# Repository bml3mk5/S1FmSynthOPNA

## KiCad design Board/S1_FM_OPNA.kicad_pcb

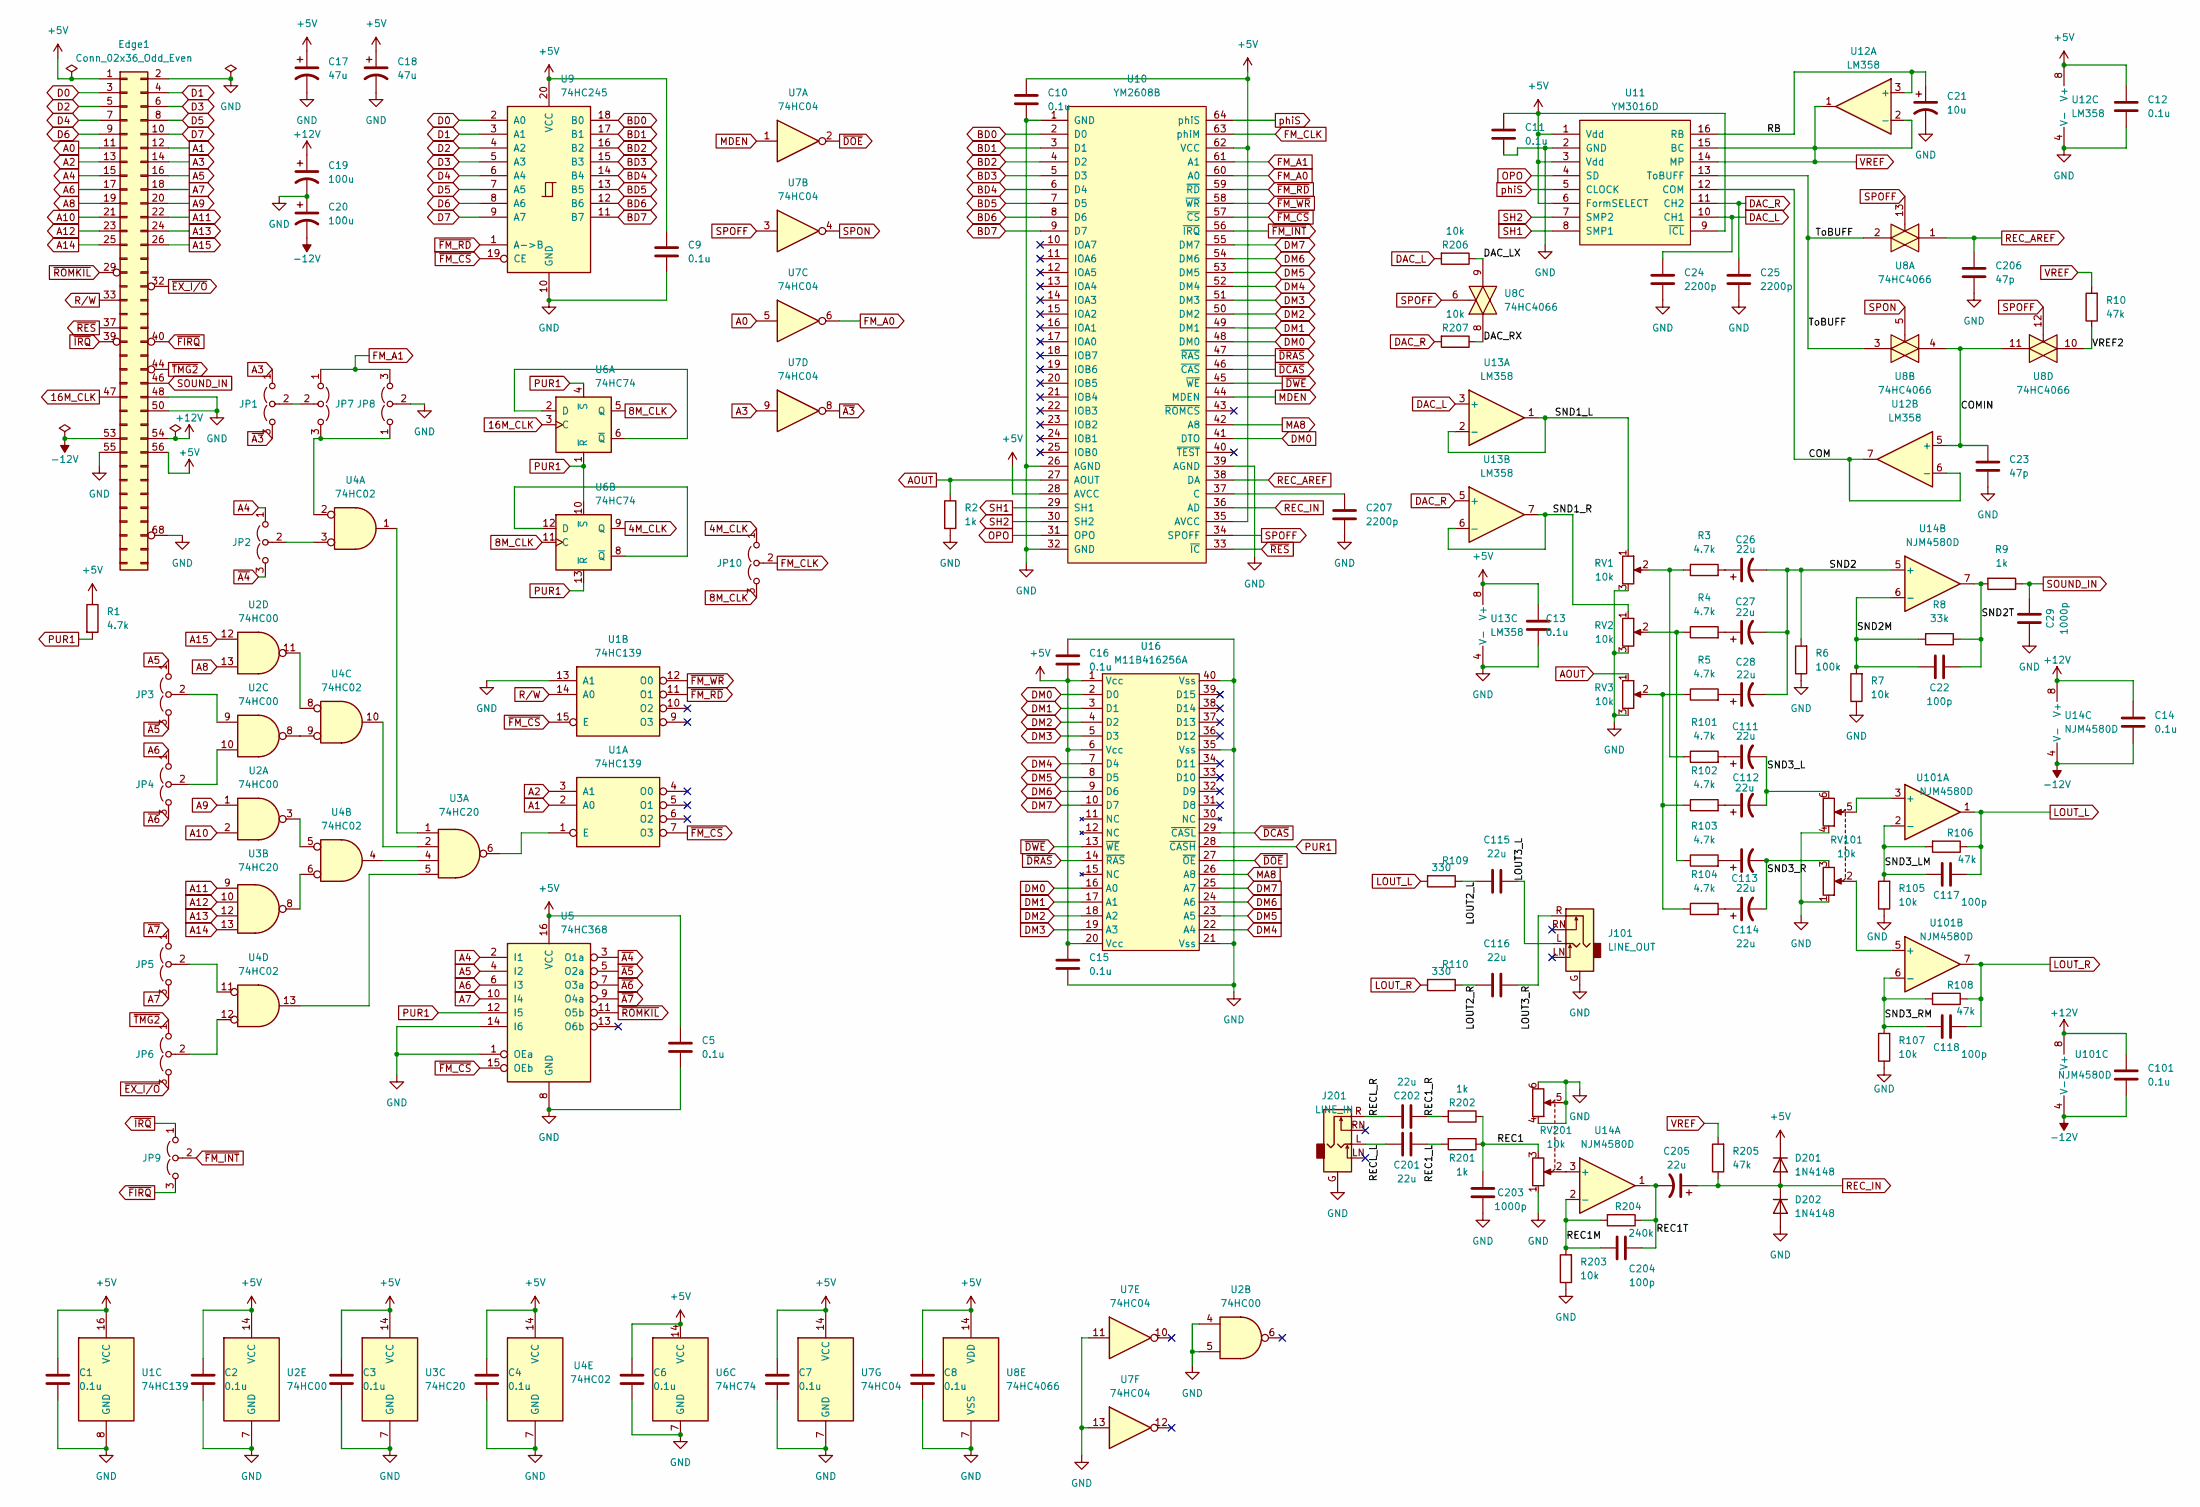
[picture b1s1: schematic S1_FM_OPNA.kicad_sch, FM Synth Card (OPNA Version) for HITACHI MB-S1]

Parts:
C1, C2, C3, C4, C5, C6, C7, C8, C9, C10, C11, C12, C13, C14, C15, C16, C101: 0.1u; C_Disc_D3.0mm_W1.6mm_P2.50mm
C17, C18: 47u; CP_Radial_D6.3mm_P2.50mm
C19, C20: 100u; CP_Radial_D6.3mm_P2.50mm
C21: 10u; CP_Radial_D5.0mm_P2.50mm
C22, C117, C118, C204: 100p; C_Disc_D3.0mm_W1.6mm_P2.50mm
C23, C206: 47p; C_Disc_D3.0mm_W1.6mm_P2.50mm
C24, C25, C207: 2200p; C_Disc_D3.0mm_W1.6mm_P2.50mm
C26, C27, C28, C111, C112, C113, C114, C205: 22u; CP_Radial_D5.0mm_P2.50mm
C29, C203: 1000p; C_Disc_D3.0mm_W1.6mm_P2.50mm
C115, C116, C201, C202: 22u; C_Radial_D6.3mm_H5.0mm_P2.50mm
D201, D202: 1N4148; D_DO-34_SOD68_P7.62mm_Horizontal
Edge1: Conn_02x36_Odd_Even; CardEdge72
J101: LINE_OUT; Jack_3.5mm_CUI_PJ317_Horizontal_X
J201: LINE_IN; Jack_3.5mm_CUI_PJ317_Horizontal_X
JP1, JP2, JP3, JP4, JP5, JP6, JP7, JP8, JP9, JP10: Jumper_3_Open; PinHeader_1x03_P2.54mm_Vertical
R1: 4.7k; R_Axial_DIN0207_L6.3mm_D2.5mm_P2.54mm_Vertical
R2, R9, R201, R202: 1k; R_Axial_DIN0207_L6.3mm_D2.5mm_P7.62mm_Horizontal
R3, R4, R5, R101, R102, R103, R104: 4.7k; R_Axial_DIN0207_L6.3mm_D2.5mm_P7.62mm_Horizontal
R6: 100k; R_Axial_DIN0207_L6.3mm_D2.5mm_P7.62mm_Horizontal
R7, R105, R107, R203, R206, R207: 10k; R_Axial_DIN0207_L6.3mm_D2.5mm_P7.62mm_Horizontal
R8: 33k; R_Axial_DIN0207_L6.3mm_D2.5mm_P7.62mm_Horizontal
R10, R106, R108, R205: 47k; R_Axial_DIN0207_L6.3mm_D2.5mm_P7.62mm_Horizontal
R109, R110: 330; R_Axial_DIN0207_L6.3mm_D2.5mm_P7.62mm_Horizontal
R204: 240k; R_Axial_DIN0207_L6.3mm_D2.5mm_P7.62mm_Horizontal
RV1, RV2, RV3: 10k; Potentiometer_Vishay_T73YP_Vertical
RV101, RV201: 10k; Potentiometer_Alps_RK097_Dual_Horizontal_X
U1: 74HC139; DIP-16_W7.62mm_Socket
U2: 74HC00; DIP-14_W7.62mm_Socket
U3: 74HC20; DIP-14_W7.62mm_Socket
U4: 74HC02; DIP-14_W7.62mm_Socket
U5: 74HC368; DIP-16_W7.62mm_Socket
U6: 74HC74; DIP-14_W7.62mm_Socket
U7: 74HC04; DIP-14_W7.62mm_Socket
U8: 74HC4066; DIP-14_W7.62mm_Socket
U9: 74HC245; DIP-20_W7.62mm_Socket
U10: YM2608B; SDIP-64
U11: YM3016D; DIP-16_W7.62mm_Socket
U12, U13: LM358; DIP-8_W7.62mm_Socket
U14, U101: NJM4580D; DIP-8_W7.62mm_Socket
U16: M11B416256A; SOIC-40

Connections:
4M_CLK: JP10.1 (A), U6.9 (Q)
8M_CLK: JP10.3 (B), U6.5 (Q), U6.11 (C)
16M_CLK: Edge1.47 (16M_CLK), U6.3 (C)
+5V: C1.1, C2.1, C3.1, C4.1, C5.1, C6.1, C7.1, C8.1, C9.1, C10.1, C11.1, C12.1, C13.1, C15.1, C16.2, C17.1, C18.1, D201.1 (K), Edge1.1 (Vcc), Edge1.56 (Vcc), R1.1, U1.16 (VCC), U2.14 (VCC), U3.14 (VCC), U4.14 (VCC), U5.16 (VCC), U6.14 (VCC), U7.14 (VCC), U8.14 (VDD), U9.20 (VCC), U10.28 (AVCC), U10.35 (AVCC), U10.62 (VCC), U11.1 (Vdd), U11.3 (Vdd), U11.6 (FormSELECT), U11.9 (~ICL), U12.8 (V+), U13.8 (V+), U16.1 (Vcc), U16.6 (Vcc), U16.20 (Vcc)
+12V: C14.1, C19.1, C101.1, Edge1.54 (+12V), U14.8 (V+), U101.8 (V+)
-12V: C14.2, C20.2, C101.2, Edge1.53 (-12V), U14.4 (V-), U101.4 (V-)
/COM: U11.12 (COM), U12.6 (-), U12.7
/COMIN: C23.1, U8.4, U8.11, U12.5 (+)
/DAC_LX: R206.1, U8.9
/DAC_RX: R207.1, U8.8
/LOUT2_L: C115.1, R109.1
/LOUT2_R: C116.1, R110.1
/LOUT3_L: C115.2, J101.L
/LOUT3_R: C116.2, J101.R
/RB: C21.1, U11.16 (RB), U12.3 (+)
/REC1: C203.1, R201.1, R202.1, RV201.3
/REC1M: C204.2, R203.2, R204.2, U14.2 (-)
/REC1T: C204.1, C205.2, R204.1, U14.1
/REC1_L: C201.2, R201.2
/REC1_R: C202.2, R202.2
/RECL_L: C201.1, J201.L
/RECL_R: C202.1, J201.R
/SND1_L: RV1.1, U13.1, U13.2 (-)
/SND1_R: RV2.1, U13.6 (-), U13.7
/SND2: C26.2, C27.2, C28.2, R6.2, U14.5 (+)
/SND2M: C22.2, R7.2, R8.2, U14.6 (-)
/SND2T: C22.1, R8.1, R9.2, U14.7
/SND3_L: C111.2, C112.2, RV101.6
/SND3_LM: C117.2, R105.2, R106.2, U101.2 (-)
/SND3_R: C113.2, C114.2, RV101.3
/SND3_RM: C118.2, R107.2, R108.2, U101.6 (-)
/ToBUFF: U8.2, U8.3, U11.13 (ToBUFF)
/VREF2: R10.1, U8.10
A0: Edge1.11 (A0), U7.5
A1: Edge1.12 (A1), U1.2 (A0)
A2: Edge1.13 (A2), U1.3 (A1)
A3: Edge1.14 (A3), JP1.1 (A), U7.9
A4: Edge1.15 (A4), JP2.1 (A), U5.2 (I1)
A5: Edge1.16 (A5), JP3.1 (A), U5.4 (I2)
A6: Edge1.17 (A6), JP4.1 (A), U5.6 (I3)
A7: Edge1.18 (A7), JP5.3 (B), U5.10 (I4)
A8: Edge1.19 (A8), U2.13
A9: Edge1.20 (A9), U2.1
A10: Edge1.21 (A10), U2.2
A11: Edge1.22 (A11), U3.9
A12: Edge1.23 (A12), U3.10
A13: Edge1.24 (A13), U3.12
A14: Edge1.25 (A14), U3.13
A15: Edge1.26 (A15), U2.12
AOUT: R2.1, RV3.1, U10.27 (AOUT)
BD0: U9.18 (B0), U10.2 (D0)
BD1: U9.17 (B1), U10.3 (D1)
BD2: U9.16 (B2), U10.4 (D2)
BD3: U9.15 (B3), U10.5 (D3)
BD4: U9.14 (B4), U10.6 (D4)
BD5: U9.13 (B5), U10.7 (D5)
BD6: U9.12 (B6), U10.8 (D6)
BD7: U9.11 (B7), U10.9 (D7)
D0: Edge1.3 (D0), U9.2 (A0)
D1: Edge1.4 (D1), U9.3 (A1)
D2: Edge1.5 (D2), U9.4 (A2)
D3: Edge1.6 (D3), U9.5 (A3)
D4: Edge1.7 (D4), U9.6 (A4)
D5: Edge1.8 (D5), U9.7 (A5)
D6: Edge1.9 (D6), U9.8 (A6)
D7: Edge1.10 (D7), U9.9 (A7)
DAC_L: C24.1, R206.2, U11.10 (CH1), U13.3 (+)
DAC_R: C25.1, R207.2, U11.11 (CH2), U13.5 (+)
DM0: U10.41 (DTO), U10.48 (DM0), U16.2 (D0), U16.16 (A0)
DM1: U10.49 (DM1), U16.3 (D1), U16.17 (A1)
DM2: U10.50 (DM2), U16.4 (D2), U16.18 (A2)
DM3: U10.51 (DM3), U16.5 (D3), U16.19 (A3)
DM4: U10.52 (DM4), U16.7 (D4), U16.22 (A4)
DM5: U10.53 (DM5), U16.8 (D5), U16.23 (A5)
DM6: U10.54 (DM6), U16.9 (D6), U16.24 (A6)
DM7: U10.55 (DM7), U16.10 (D7), U16.25 (A7)
FM_A0: U7.6, U10.60 (A0)
FM_A1: JP7.1 (A), JP8.3 (B), U10.61 (A1)
FM_CLK: JP10.2 (C), U10.63 (phiM)
GND: C1.2, C2.2, C3.2, C4.2, C5.2, C6.2, C7.2, C8.2, C9.2, C10.2, C11.2, C12.2, C13.2, C15.2, C16.1, C17.2, C18.2, C19.2, C20.1, C21.2, C23.2, C24.2, C25.2, C29.2, C203.2, C206.2, C207.2, D202.2 (A), Edge1.2 (GND), Edge1.48 (GND), Edge1.50 (GND), Edge1.55 (GND), Edge1.68 (~S1_IF_SEL), J101.G, J201.G, JP8.2 (C), R2.2, R6.1, R7.1, R105.1, R107.1, R203.1, RV1.3, RV2.3, RV3.3, RV101.1, RV101.4, RV201.1, RV201.4, RV201.5, RV201.6, U1.8 (GND), U1.13 (A1), U2.4, U2.5, U2.7 (GND), U3.7 (GND), U4.7 (GND), U5.1 (OEa), U5.8 (GND), U5.14 (I6), U6.7 (GND), U7.7 (GND), U7.11, U7.13, U8.7 (VSS), U9.10 (GND), U10.1 (GND), U10.26 (AGND), U10.32 (GND), U10.39 (AGND), U11.2 (GND), U12.4 (V-), U13.4 (V-), U16.21 (Vss), U16.35 (Vss), U16.40 (Vss)
LOUT_L: C117.1, R106.1, R109.2, U101.1
LOUT_R: C118.1, R108.1, R110.2, U101.7
MA8: U10.42 (A8), U16.26 (A8)
MDEN: U7.1, U10.44 (MDEN)
unnamed: C26.1, R3.2
unnamed: C27.1, R4.2
unnamed: C28.1, R5.2
unnamed: C111.1, R101.2
unnamed: C112.1, R102.2
unnamed: C113.1, R103.2
unnamed: C114.1, R104.2
unnamed: C207.1, U10.37 (C)
unnamed: JP1.2 (C), JP7.2 (C)
unnamed: JP2.2 (C), U4.3
unnamed: JP3.2 (C), U2.9
unnamed: JP4.2 (C), U2.10
unnamed: JP5.2 (C), U4.11
unnamed: JP6.2 (C), U4.12
unnamed: JP7.3 (B), JP8.1 (A), U4.2
unnamed: R3.1, R101.1, RV1.2
unnamed: R5.1, R102.1, R104.1, RV3.2
unnamed: R4.1, R103.1, RV2.2
unnamed: RV101.2, U101.5 (+)
unnamed: RV101.5, U101.3 (+)
unnamed: RV201.2, U14.3 (+)
unnamed: U1.1 (E), U3.6
unnamed: U2.3, U4.5
unnamed: U2.8, U4.9
unnamed: U2.11, U4.8
unnamed: U3.1, U4.1
unnamed: U3.2, U4.10
unnamed: U3.4, U4.4
unnamed: U3.5, U4.13
unnamed: U3.8, U4.6
unnamed: U6.2 (D), U6.6 (~Q)
unnamed: U6.8 (~Q), U6.12 (D)
OPO: U10.31 (OPO), U11.4 (SD)
PUR1: R1.2, U5.12 (I5), U6.1 (~R), U6.4 (~S), U6.10 (~S), U6.13 (~R), U16.28 (~CASH)
REC_AREF: C206.1, U8.1, U10.38 (DA)
REC_IN: C205.1, D201.2 (A), D202.1 (K), R205.1, U10.36 (AD)
R/W: Edge1.33 (R/W_OUT), U1.14 (A0)
SH1: U10.29 (SH1), U11.8 (SMP1)
SH2: U10.30 (SH2), U11.7 (SMP2)
SOUND_IN: C29.1, Edge1.46 (SOUND_IN), R9.1
SPOFF: U7.3, U8.6, U8.12, U8.13, U10.34 (SPOFF)
SPON: U7.4, U8.5
VREF: R10.2, R205.2, U11.14 (MP), U11.15 (BC), U12.1, U12.2 (-)
phiS: U10.64 (phiS), U11.5 (CLOCK)
~A3: JP1.3 (B), U7.8
~A4: JP2.3 (B), U5.3 (O1a)
~A5: JP3.3 (B), U5.5 (O2a)
~A6: JP4.3 (B), U5.7 (O3a)
~A7: JP5.1 (A), U5.9 (O4a)
~DCAS: U10.46 (~CAS), U16.29 (~CASL)
~DOE: U7.2, U16.27 (~OE)
~DRAS: U10.47 (~RAS), U16.14 (~RAS)
~DWE: U10.45 (~WE), U16.13 (~WE)
~EX_I/O: Edge1.32 (~EX_I/O), JP6.3 (B)
~FIRQ: Edge1.40 (~FIRQ), JP9.3 (B)
~FM_CS: U1.7 (O3), U1.15 (E), U5.15 (OEb), U9.19 (CE), U10.57 (~CS)
~FM_INT: JP9.2 (C), U10.56 (~IRQ)
~FM_RD: U1.11 (O1), U9.1 (A->B), U10.59 (~RD)
~FM_WR: U1.12 (O0), U10.58 (~WR)
~IRQ: Edge1.39 (~IRQ), JP9.1 (A)
~RES: Edge1.37 (~RES), U10.33 (~IC)
~ROMKIL: Edge1.29 (~ROMKIL), U5.11 (O5b)
~TMG2: Edge1.44 (~TMG2), JP6.1 (A)

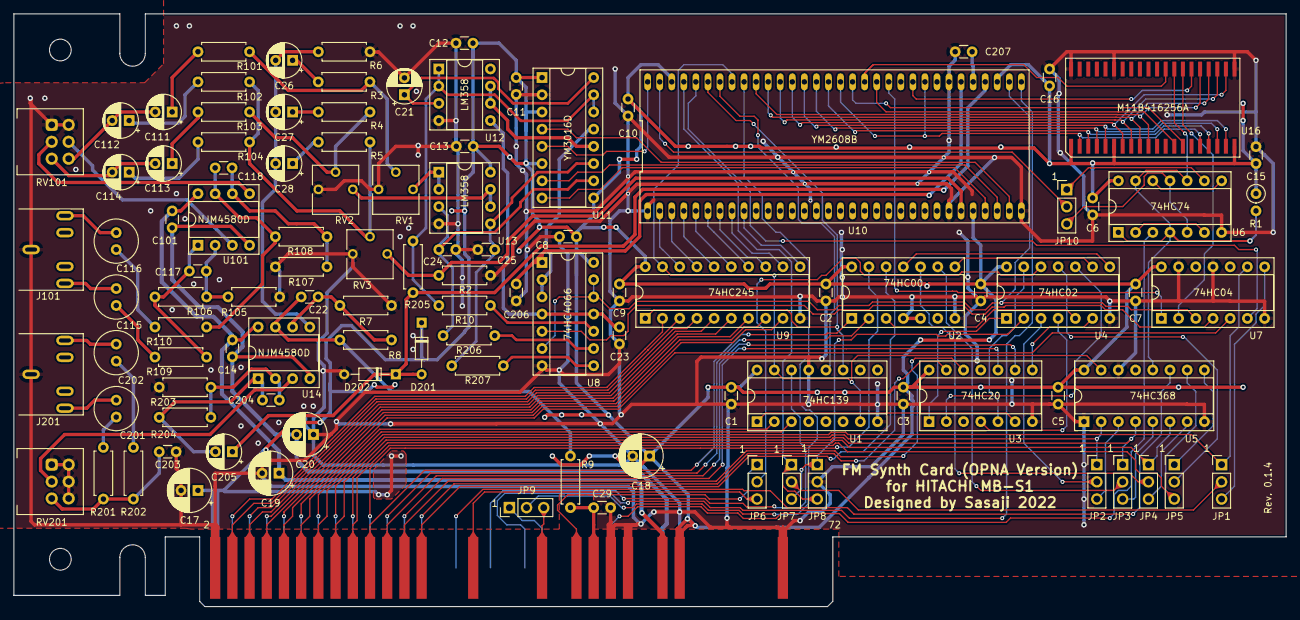
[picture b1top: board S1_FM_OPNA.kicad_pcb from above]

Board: 2 copper layers, 187.8 x 87.5 mm, 108 parts (0 on the bottom side), 147 nets.

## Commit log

2023-08-09 Revision 0.1.4
2023-08-10 Modify documents
